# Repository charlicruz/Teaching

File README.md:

# Recursos Académicos – Electrónica | Universidad de Alcalá

Este repositorio agrupa contenidos didácticos y materiales desarrollados para distintas asignaturas del área de **Electrónica** impartidas en la **Universidad de Alcalá (UAH)**.  
Incluye **ejercicios, proyectos, guías de laboratorio, simulaciones, diseños PCB y vídeos explicativos**, orientados a estudiantes de ingeniería.

---

## 📚 Asignaturas incluidas

### 🔌 Digital_Electronics  
Diseño de sistemas digitales mediante VHDL, lógica combinacional y secuencial, implementación en FPGAs y simulación con testbenches.
https://github.com/charlicruz/Teaching/tree/main/Digital_Electronics

### 🛠 Electronic Design  
Ejercicios y proyectos centrados en el diseño de sistemas electrónicos digitales y analógicos, incluyendo el uso de herramientas como Quartus, ModelSim, y herramientas de simulación.
https://github.com/charlicruz/Teaching/tree/main/Electronic%20Design

### 💡 Electronics Fundamentals  
Material introductorio sobre análisis de circuitos, componentes básicos, ley de Ohm, ley de Kirchhoff, amplificadores, filtros, y fundamentos de electrónica digital.
https://github.com/charlicruz/Teaching/tree/main/Electronics_Fundamentals

### ⚙️ Electronic Technology  
Diseño electrónico aplicado: prácticas de laboratorio, diseño de PCB, simulaciones en LTspice, montaje de prototipos, y validación experimental.
https://github.com/charlicruz/Teaching/tree/main/Electronic_Technology

### 🔍 Forensic Electronics  

Aplicaciones de la electrónica en entornos forenses: análisis de señales, recuperación de evidencias, instrumentación avanzada y documentación técnica.
https://github.com/charlicruz/Teaching/tree/main/Forensic_Electronics

---

## 📂 Estructura común del repositorio

```text
/asignatura/
  /videos/             # Tutoriales y explicaciones en vídeo
  /ejercicios/         # Ejercicios propuestos y resueltos
  /proyectos/          # Proyectos de diseño y simulación
  /pcb_design/         # Diseño de PCB (KiCad, Proteus, etc.)
  /simulaciones/

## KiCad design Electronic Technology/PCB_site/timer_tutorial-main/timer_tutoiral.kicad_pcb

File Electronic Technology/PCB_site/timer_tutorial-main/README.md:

# Timer Tutorial

This is a 555 timer based project for new electronics team members to wet their feet in the world of hardware design and prototyping, *without needing to do any coding!*

The goal is simple, have new members design an LED blinker using a 555-timer chip to flash at about 0.5 Hz. Ideally they start by reading and digesting the datasheet for the 555 timer (included as a PDF in this repository) and working their way to a circuit board in KiCad with some prototyping inbetween so they get experience with all stages of a circuit bring up.

In addition to the 555 datasheet, a complete KiCad project for this project is also included. **New members should make their own projects from scratch** as part of this exercise but this can be distributed to late joiners or used as a reference when lecturing about KiCad. 

### New Member Prepartion

**New members shouldn't really be expected to prepare for this project** *(at least for the first (prototyping) part)*. All prototyping materials should be prepared by the head of electronics in advance. Luckily nothing is needed for this that isn't usually laying around McCaul already, except for perhaps some 555 chips.

For teaching/learning KiCad it is helpful for each member to have their own laptop with the latest version of KiCad pre-installed so they can follow along instead of just watching. This can easily be "homework" if the project is borken between multiple sessions.

# The Project

The task for this project is simple, create a blinker that could be used as an indicating light for when a bike needs to turn. Just like with a car, the blinking needs to be perceptible so neither too fast nor too slow, roughly a second of the LED being on followed by a second of it being off is adequate.

To accomplish this we are going to use a 555 timer chip, arguably the most produced integrated circuit (IC) ever and a common gateway chip to hobby electronics. It can be used many different ways so one must read the documentation on the chip in the form a datasheet and then determine how to proceed with the design.

Once familiar with the chip and a rough design is settled on, we can embark on the rest of the electronics design process! Ideally with a nice flashy prototype by the end of it.

## Process

This project is meant to be reflective of the general electronics development process. In general the following steps are completed in roughly this order, not too disimilar to the flow of a majority of engineering projects:

1. **Determining the scope of a project.** _What are our inputs/outputs? What can/can't we use? Etc._
2. **Research into parts.** _Reading data sheets, reviewing reference designs, seeing other people's work._
3. **Building [breadboard] prototypes.** _Building circuits with non-perfect/non-exact components (e.g. no 1253.7 Ohm resistors), learning about component polarity, __verifying connections__!_
4. **Assessing circuit performance.** _Determining expected behaviour, using measurement equipment like multimeters and oscilloscopes._
5. **Iterating on design as needed.** _Adjusting component values, re-reading documentation, verifying calculations._
6. **Transcribing circuit schematic into Electronics Design Assistant (EDA).** _Start operating KiCad schematic tool._
7. **Designing circuit board in EDA.** _Using more KiCad, selecting footprints, introduction into design for assembly/manufacturing._

Going through all these steps in a single session, especially when starting out is unlikely without it feeling rushed or a marathon of a session. Consider doing the prototyping in one large session with a shorter follow-up session for the EDA portion, this also gives them time to install KiCad at home in advance of the KiCad session. _(Protip: it is much easier when teaching larger groups to have everyone at a similar stage in the process.)_

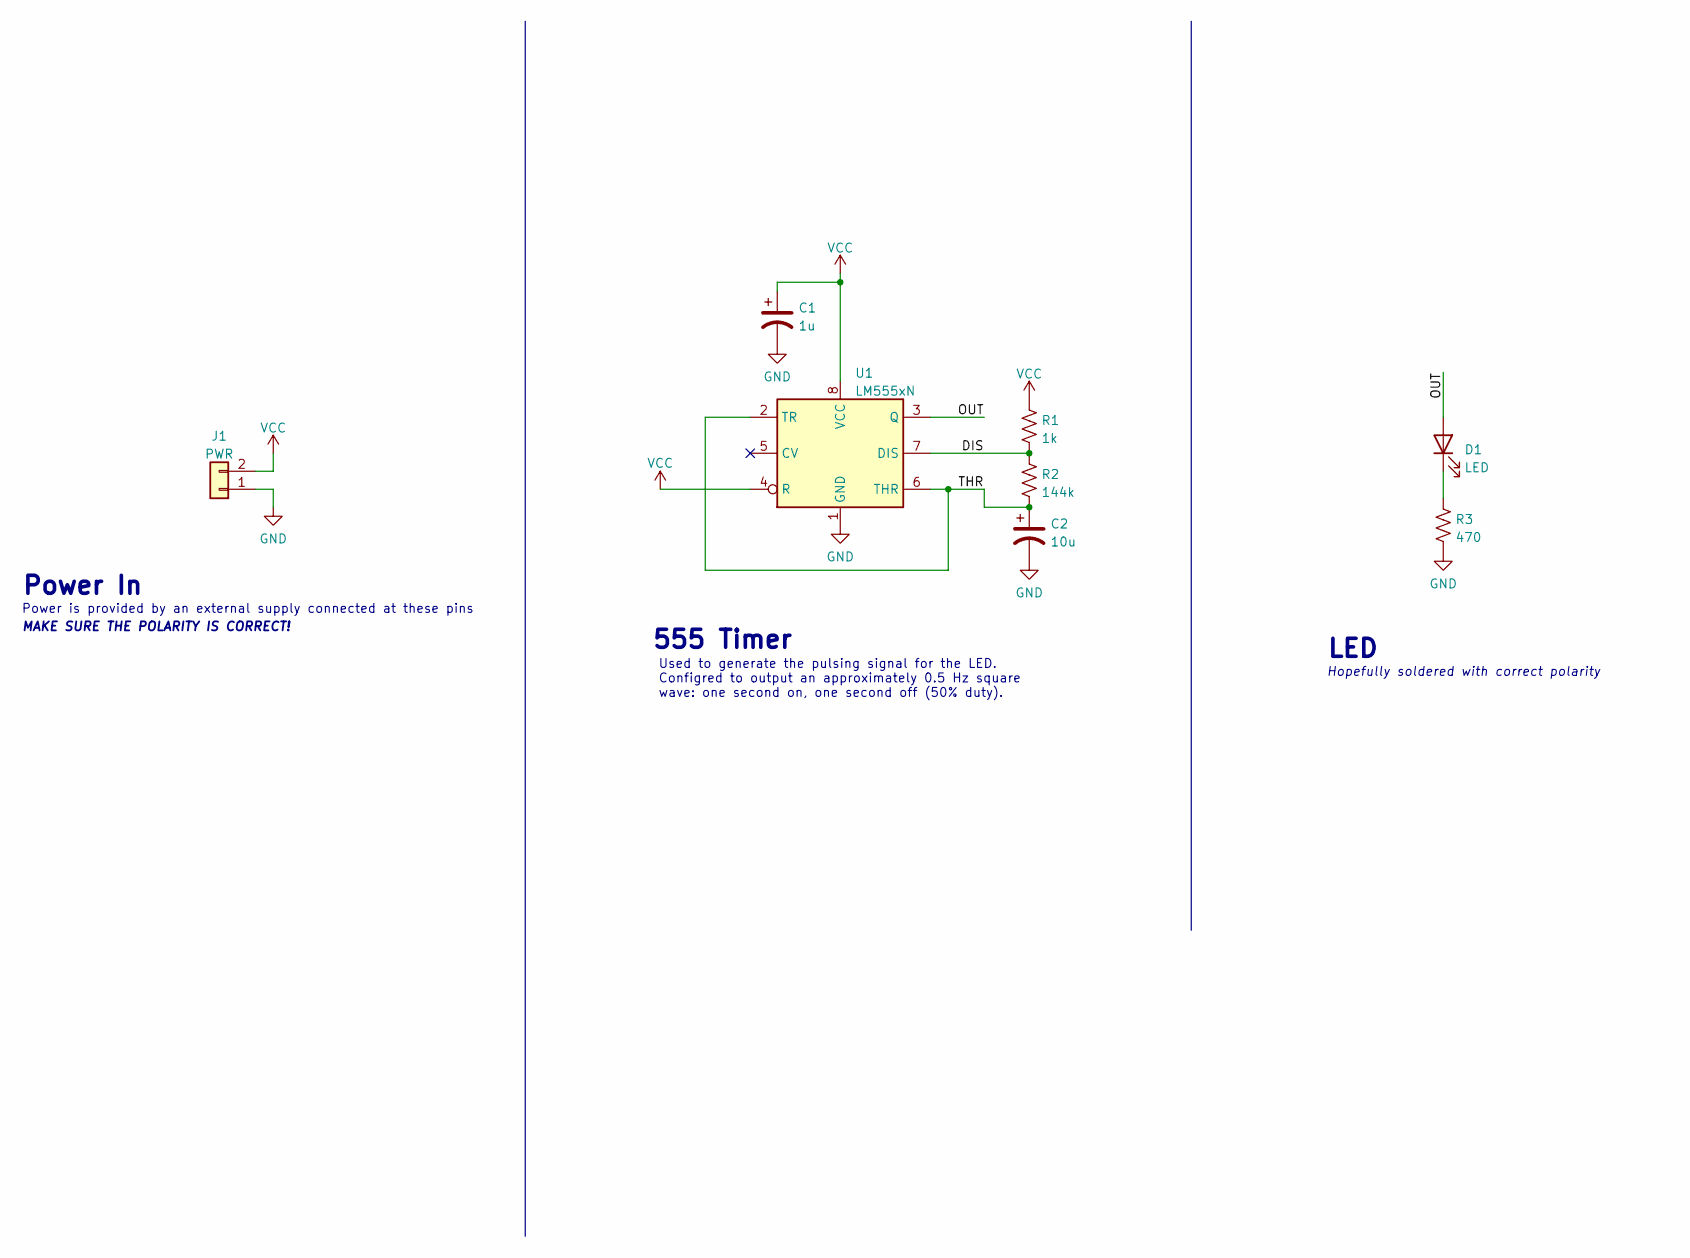
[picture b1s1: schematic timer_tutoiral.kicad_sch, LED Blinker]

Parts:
C1: 1u; CP_Radial_D4.0mm_P2.00mm
C2: 10u; CP_Radial_D4.0mm_P2.00mm
D1: LED; LED_D4.0mm
J1: PWR; PinSocket_1x02_P2.54mm_Vertical
R1: 1k; R_Axial_DIN0207_L6.3mm_D2.5mm_P10.16mm_Horizontal
R2: 144k; R_Axial_DIN0207_L6.3mm_D2.5mm_P10.16mm_Horizontal
R3: 470; R_Axial_DIN0207_L6.3mm_D2.5mm_P10.16mm_Horizontal
U1: LM555xN; DIP-8_W7.62mm

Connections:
/DIS: R1.2, R2.1, U1.7 (DIS)
/OUT: D1.2 (A), U1.3 (Q)
/THR: C2.1, R2.2, U1.2 (TR), U1.6 (THR)
GND: C1.2, C2.2, J1.1, R3.2, U1.1 (GND)
unnamed: D1.1 (K), R3.1
VCC: C1.1, J1.2, R1.1, U1.4 (R), U1.8 (VCC)

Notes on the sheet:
Power In
LED
Hopefully soldered with correct polarity
MAKE SURE THE POLARITY IS CORRECT!
Power is provided by an external supply connected at these pins
555 Timer
Used to generate the pulsing signal for the LED. Configred to output an approximately 0.5 Hz square wave: one second on, one second off (50% duty).

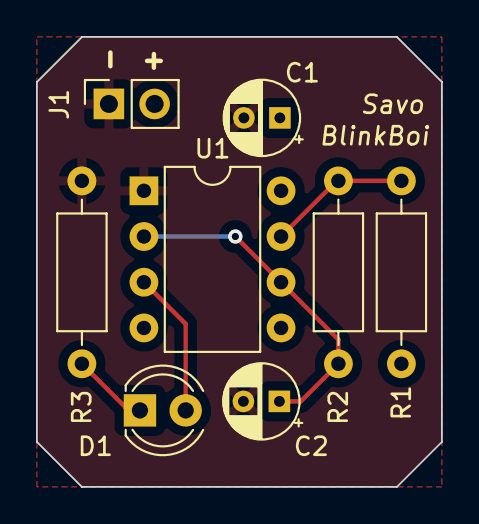
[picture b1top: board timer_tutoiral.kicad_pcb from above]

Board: 2 copper layers, 22.5 x 25.0 mm, 8 parts (0 on the bottom side), 6 nets.

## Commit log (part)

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2025-06-15 Create Tutorial Quartus
2025-06-15 Update Tutorial Quartus
2025-06-15 Add files via upload
    Electronics Design with VHDL: questions" by Dr. Carlos Cruz de la Torre from the University of Alcalá, focuses on various aspects of digital design using VHDL. It contains a comprehensive set of ques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
    Data Type Conversion: Exercises on converting std_logic_vector signals to integers.
    Logical and Relational Operators: Assessing valid logical operations and comparisons between signal values.
    Array, Record, and Signal Manipulation: Questions on assigning and manipulating bits in vectors, arrays, and records.
    VHDL Code Simulation: Challenges involving VHDL processes, signal and vari
2025-07-17 Create Wireshark
2025-07-17 wireshark
2026-01-28 podcast
